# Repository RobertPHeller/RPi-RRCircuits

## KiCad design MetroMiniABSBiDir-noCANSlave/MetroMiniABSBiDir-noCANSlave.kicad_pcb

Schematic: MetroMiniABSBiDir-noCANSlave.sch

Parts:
C1, C2, C3, C4: .1 uf
C5: .1 uf; Mouser Part Number 581-SR295E104MAA
CON1: 7-12 V Power Bus; Mouser Part Number 490-PJ-037A
D1: BRIDGE; Mouser Part Number 750-KBL401-G
D2: DIODESCH; Mouser Part Number SB240-E3/54
IC1: MCT6H; DIP-8__300; Mouser Part Number 782-MCT6H
P1: In Track Out; Mouser Part Number 710-691249510002
P2: +5V EG EY ER WG WY WR GND; Mouser Part Number 651-1725711
P3: Next East
P4, P6: ABS Slave Bus
P5: Next West
R1: 10 Ohms; Mouser Part Number 660-MF1/4LCT52R100J
R2: 10K Ohms; Mouser Part Number 660-MF1/4LCT52R103J
R3, R4, R5, R6, R7, R8: 150 Ohms; Mouser Part Number 660-MF1/4LCT52R151J
SW1: BC CA 0 1 2 3 4 5
T1: - 7-12V +
U1: METROMINI
U2: SN75LBC179; Mouser Part Number 595-SN75LBC179P
U3: TRS202E; Mouser Part Number 595-TRS202ECN

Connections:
+5V: C5.1, P2.1, R2.1, U1.25 (5V), U2.1 (Vcc), U3.16 (Vcc)
/East Green: P2.2, R8.1
/East Red: P2.4, R6.1
/East Yellow: P2.3, R7.1
/West Green: P2.5, R5.1
/West Red: P2.7, R3.1
/West Yellow: P2.6, R4.1
GND: C2.2, C4.2, C5.2, CON1.2, IC1.5, IC1.8, P2.8, P3.1, P3.4, P4.5, P5.1, P5.4, P6.5, SW1.1, SW1.2, SW1.3, SW1.4, SW1.5, SW1.6, SW1.7, SW1.8, T1.2 (PM), U1.23 (GND), U1.24 (GND), U2.4 (GND), U3.15 (GND)
unnamed: P3.2, U3.8 (RIN2)
unnamed: P5.2, U3.14 (DOUT1)
unnamed: P5.3, U3.13 (RIN1)
unnamed: P3.3, U3.7 (DOUT2)
unnamed: U1.13 (#1), U2.3 (D)
unnamed: U1.14 (#0), U2.2 (R)
unnamed: P4.4, P6.4, U2.5 (Y)
unnamed: C1.1, U3.1 (C1+)
unnamed: C3.1, U3.4 (C2+)
unnamed: C3.2, U3.5 (C2-)
unnamed: C1.2, U3.3 (C1-)
unnamed: C4.1, U3.6 (V-)
unnamed: C2.1, U3.2 (V+)
unnamed: U1.10 (#4), U3.12 (ROUT1)
unnamed: U1.7 (#7), U3.9 (ROUT2)
unnamed: SW1.12, U1.18 (A2)
unnamed: SW1.11, U1.17 (A3)
unnamed: SW1.10, U1.16 (A4)
unnamed: SW1.9, U1.15 (A5)
unnamed: SW1.13, U1.19 (A1)
unnamed: SW1.16, U1.2 (#12)
unnamed: SW1.15, U1.12 (#2)
unnamed: SW1.14, U1.20 (A0)
unnamed: CON1.1, D2.1 (A), T1.1
unnamed: P4.2, P6.2, U2.7 (B)
unnamed: P4.3, P6.3, U2.6 (Z)
unnamed: P4.1, P6.1, U2.8 (A)
unnamed: D1.1 (+), D1.4 (-)
unnamed: R8.2, U1.11 (#3)
unnamed: R4.2, U1.4 (#10)
unnamed: R3.2, U1.3 (#11)
unnamed: D2.2 (K), U1.22 (Vin)
unnamed: R7.2, U1.9 (#5)
unnamed: R6.2, U1.8 (#6)
unnamed: R5.2, U1.5 (#9)
unnamed: D1.3, P1.1, R1.1
unnamed: IC1.6, IC1.7, R2.2, U1.6 (#8), U3.10 (DIN2), U3.11 (DIN1)
unnamed: D1.2, IC1.2, IC1.4, P1.2 (PM)
unnamed: IC1.1, IC1.3, R1.2

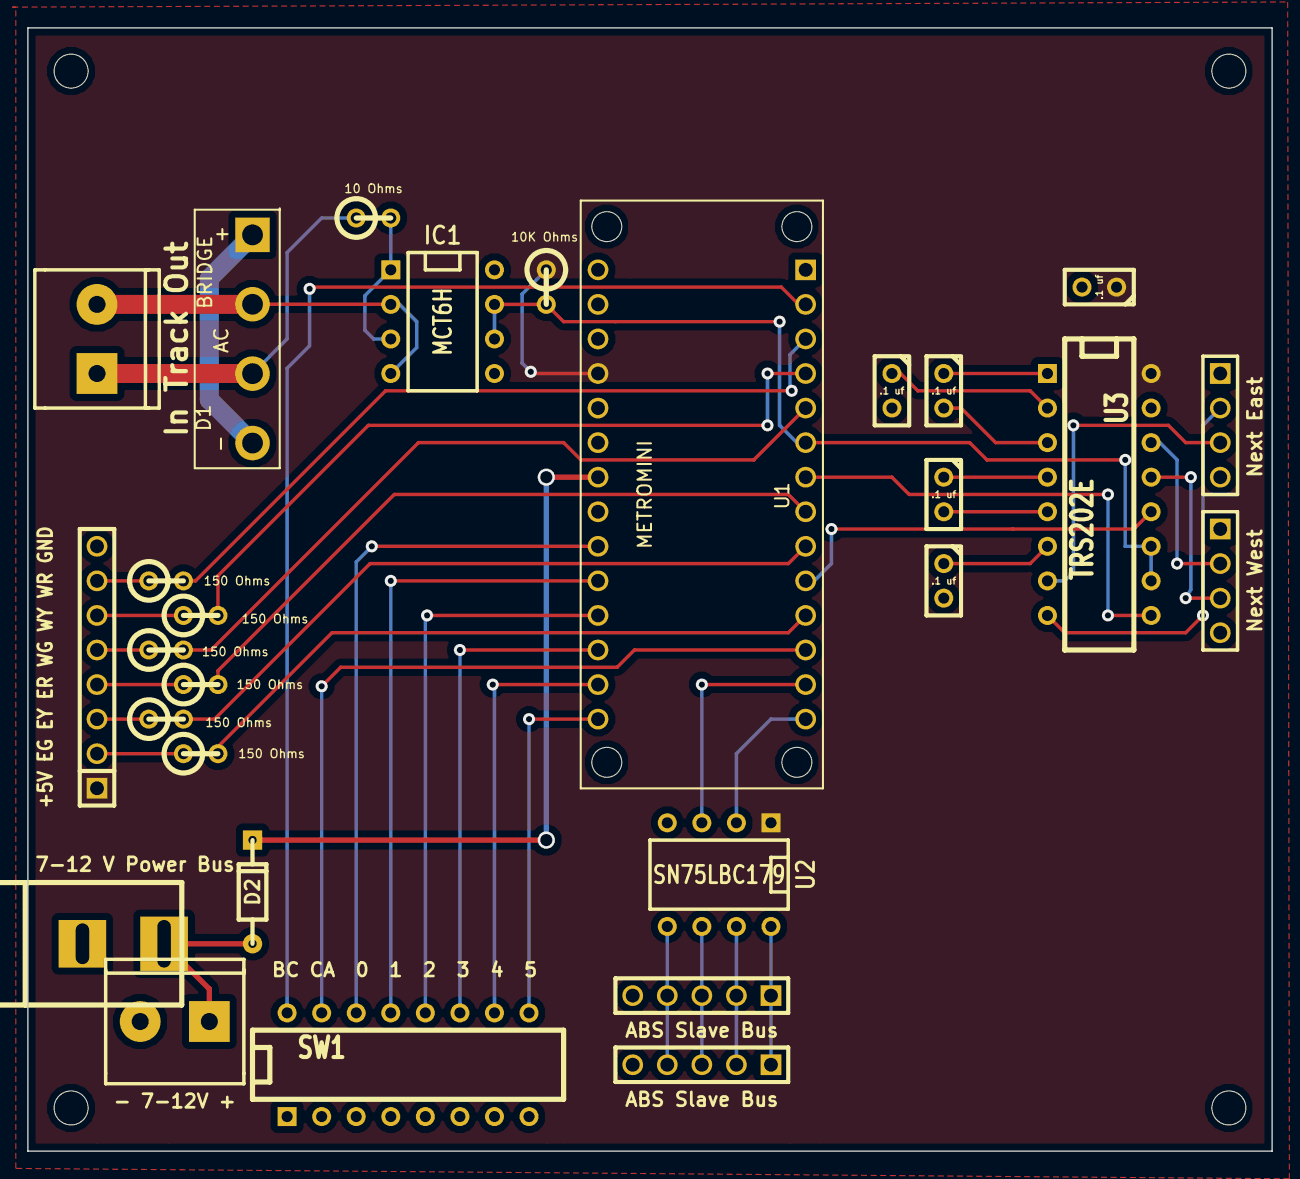
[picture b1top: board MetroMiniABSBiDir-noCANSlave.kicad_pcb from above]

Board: 2 copper layers, 91.4 x 82.5 mm, 32 parts (0 on the bottom side), 47 nets.

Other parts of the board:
MH: MountingHole_2-5mm_RevA_Date21Jun2010
MH#2, MH#3, MH#4: MountingHole_2-5mm_RevA_Date21Jun2010

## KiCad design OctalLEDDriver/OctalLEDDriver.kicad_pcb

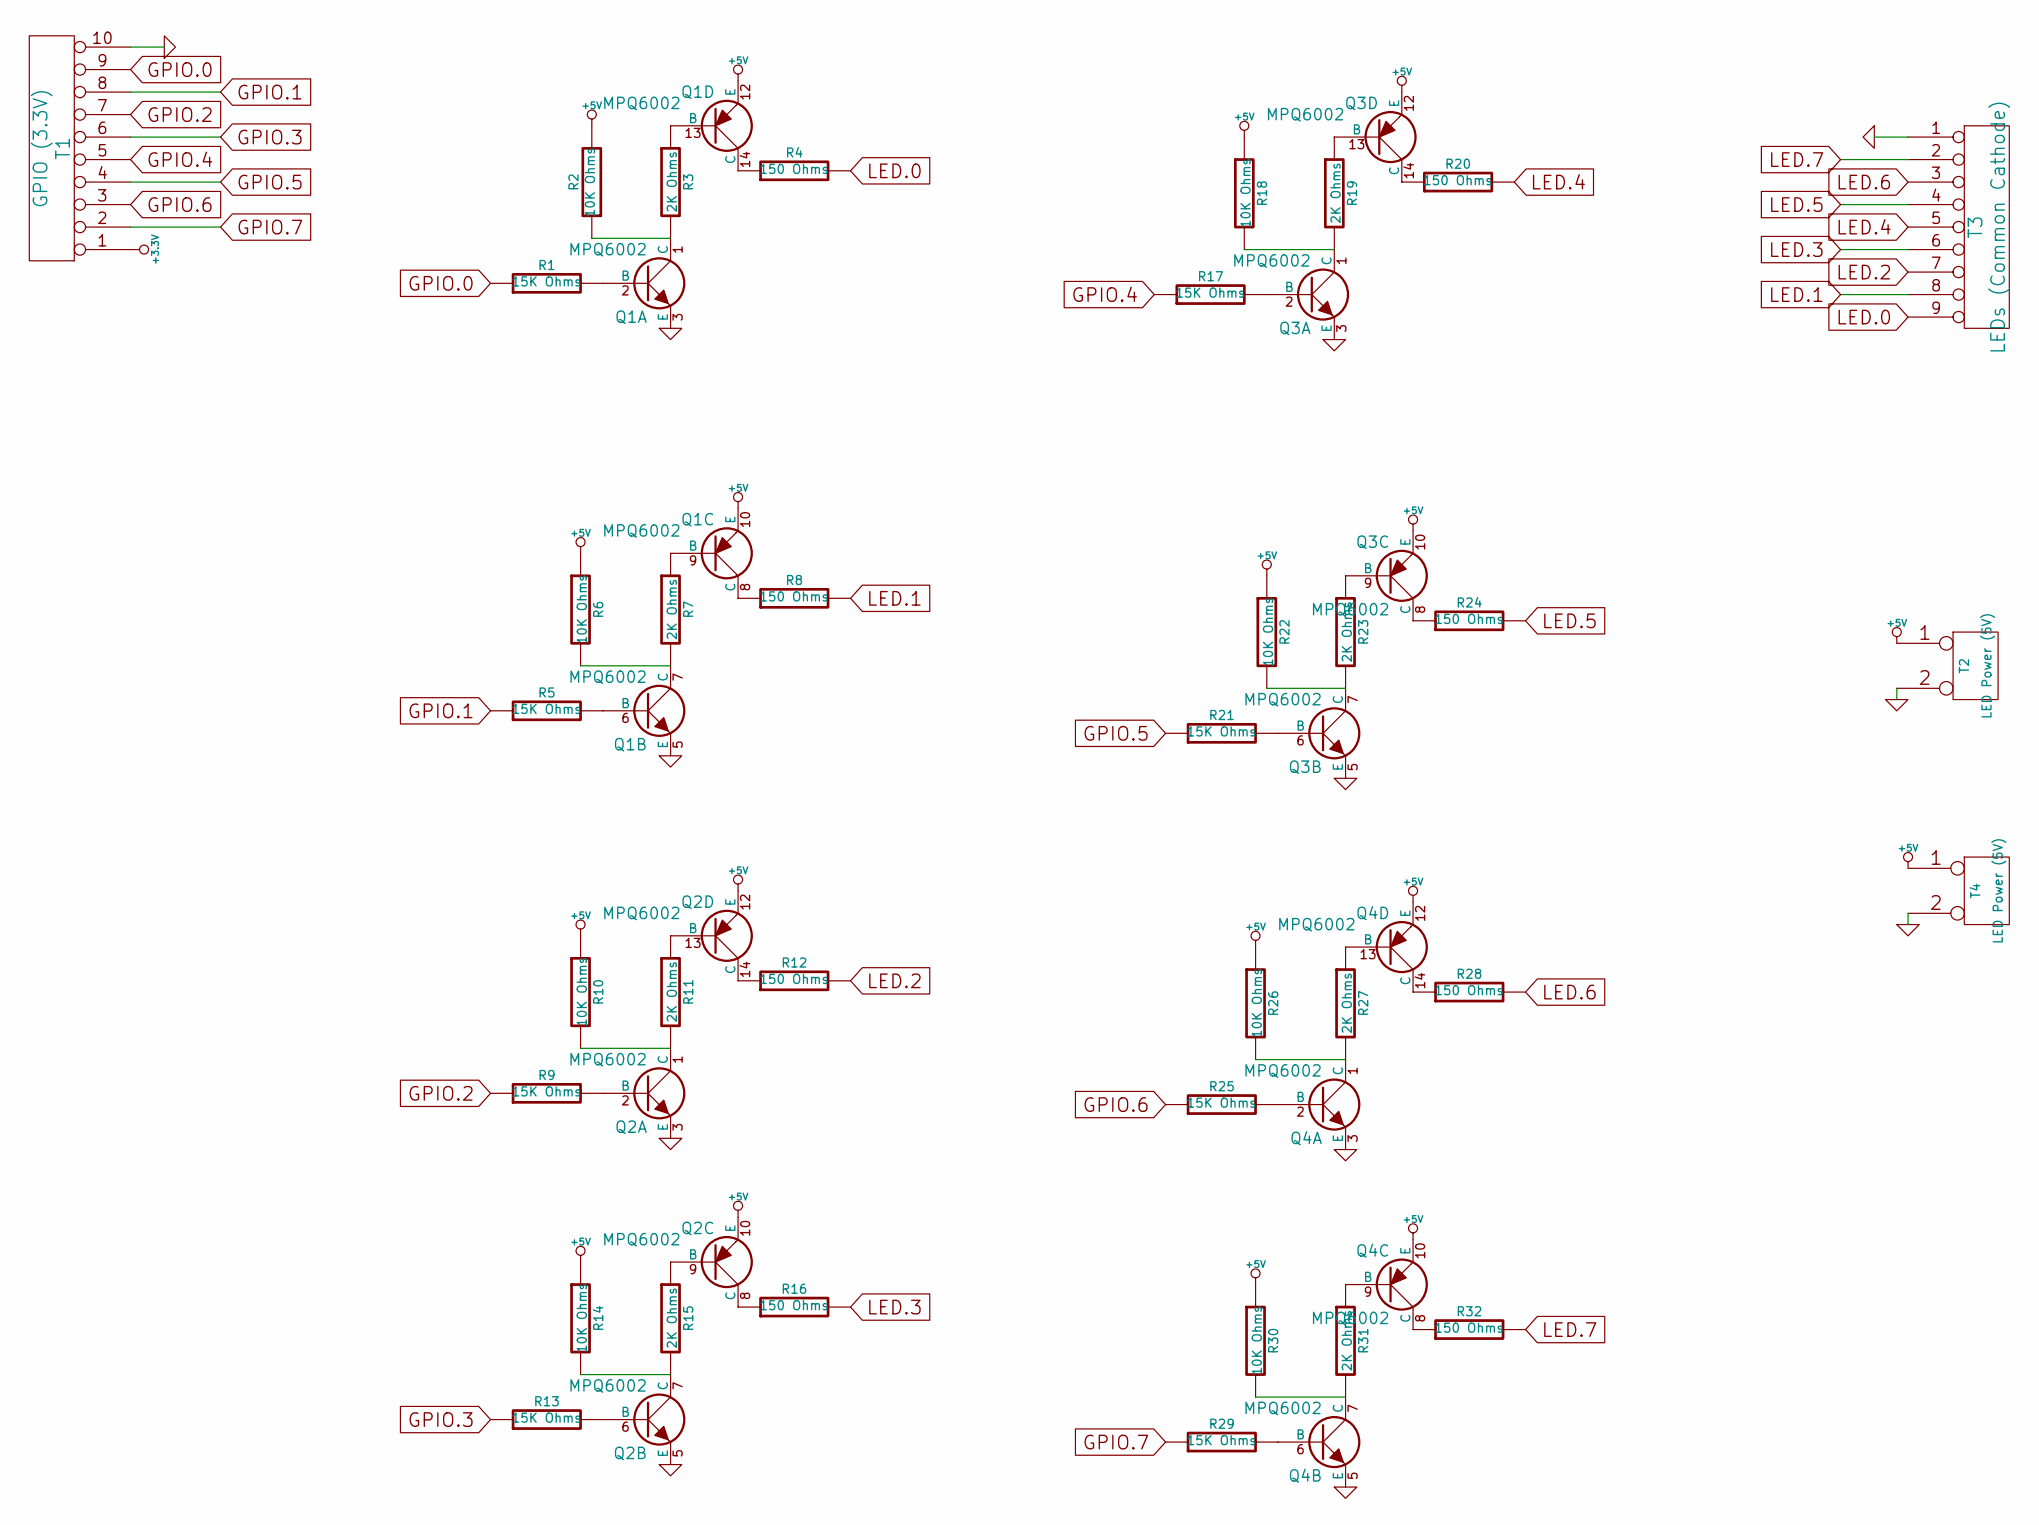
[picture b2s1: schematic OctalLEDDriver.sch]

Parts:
Q1, Q2, Q3, Q4: MPQ6002; Mouser part Number 610-MPQ6002
R1, R5, R9, R13, R17, R21, R25, R29: 15K Ohms; Mouser Part Number 603-CFR-25JR-5215K
R2, R6, R10, R14, R18, R22, R26, R30: 10K Ohms; Mouser Part Number 603-CFR-25JR-5210K
R3, R7, R11, R15, R19, R23, R27, R31: 2K Ohms; Mouser Part Number 603-CFR-25JR-522K
R4, R8, R12, R16, R20, R24, R28, R32: 150 Ohms; Mouser Part Number 588-OK1515E-R52
T1: GPIO (3.3V); Mouser Part Number 651-1725737
T2, T4: LED Power (5V); Mouser part Number 651-1725656
T3: LEDs (Common Cathode); Mouser part Number 651-1725724

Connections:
+5V: Q1.10 (E), Q1.12 (E), Q2.10 (E), Q2.12 (E), Q3.10 (E), Q3.12 (E), Q4.10 (E), Q4.12 (E), R2.2, R6.1, R10.1, R14.1, R18.1, R22.1, R26.1, R30.1, T2.1, T4.1; also elsewhere on the board
GND: Q1.3 (E), Q1.5 (E), Q2.3 (E), Q2.5 (E), Q3.3 (E), Q3.5 (E), Q4.3 (E), Q4.5 (E), T1.10, T2.2 (PM), T3.1, T4.2 (PM); also elsewhere on the board
GPIO.0: R1.1, T1.9
GPIO.1: R5.1, T1.8
GPIO.2: R9.1, T1.7
GPIO.3: R13.1, T1.6
GPIO.4: R17.1, T1.5
GPIO.5: R21.1, T1.4
GPIO.6: R25.1, T1.3
GPIO.7: R29.1, T1.2
LED.0: R4.2, T3.9
LED.1: R8.2, T3.8
LED.2: R12.2, T3.7
LED.3: R16.2, T3.6
LED.4: R20.2, T3.5
LED.5: R24.2, T3.4
LED.6: R28.2, T3.3
LED.7: R32.2, T3.2
unnamed: Q2.7 (C), R14.2, R15.2
unnamed: Q2.8 (C), R16.1
unnamed: Q3.8 (C), R24.1
unnamed: Q3.9 (B), R23.1
unnamed: Q4.8 (C), R32.1
unnamed: Q4.9 (B), R31.1
unnamed: Q3.1 (C), R18.2, R19.2
unnamed: Q3.14 (C), R20.1
unnamed: Q3.7 (C), R22.2, R23.2
unnamed: Q4.1 (C), R26.2, R27.2
unnamed: Q4.14 (C), R28.1
unnamed: Q4.7 (C), R30.2, R31.2
unnamed: Q3.6 (B), R21.2
unnamed: Q4.2 (B), R25.2
unnamed: Q4.13 (B), R27.1
unnamed: Q4.6 (B), R29.2
unnamed: Q1.13 (B), R3.1
unnamed: Q3.13 (B), R19.1
unnamed: Q2.9 (B), R15.1
unnamed: Q2.13 (B), R11.1
unnamed: Q1.9 (B), R7.1
unnamed: Q1.2 (B), R1.2
unnamed: Q1.6 (B), R5.2
unnamed: Q1.14 (C), R4.1
unnamed: Q1.8 (C), R8.1
unnamed: Q2.2 (B), R9.2
unnamed: Q2.14 (C), R12.1
unnamed: Q2.6 (B), R13.2
unnamed: Q3.2 (B), R17.2
unnamed: Q1.7 (C), R6.2, R7.2
unnamed: Q2.1 (C), R10.2, R11.2
unnamed: Q1.1 (C), R2.1, R3.2

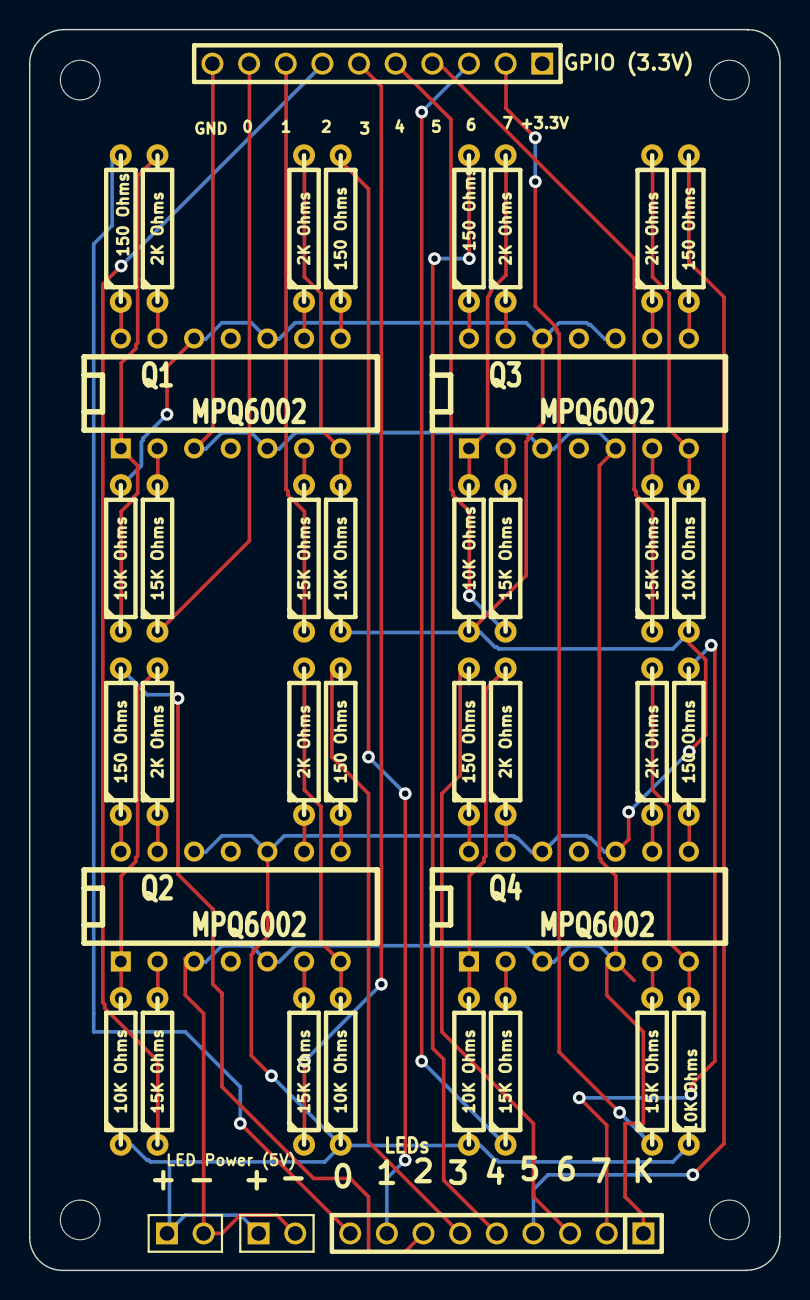
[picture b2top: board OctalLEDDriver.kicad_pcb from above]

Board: 2 copper layers, 52.0 x 86.0 mm, 40 parts (0 on the bottom side), 50 nets.

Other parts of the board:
T2#2: LED Power (5V); ScrewTerm2.54-2

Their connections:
+5V: T2#2.1; also elsewhere on the board
GND: T2#2.2; also elsewhere on the board

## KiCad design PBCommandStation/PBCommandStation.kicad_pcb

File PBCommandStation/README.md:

# PBCommandStation

Original through hole version of the Pocket Beagle LCC/DCC Command Station.
This design is depreciated -- see PocketBeagleCommandStation and 
PocketBeagleCommandStation_SMD for a current design.

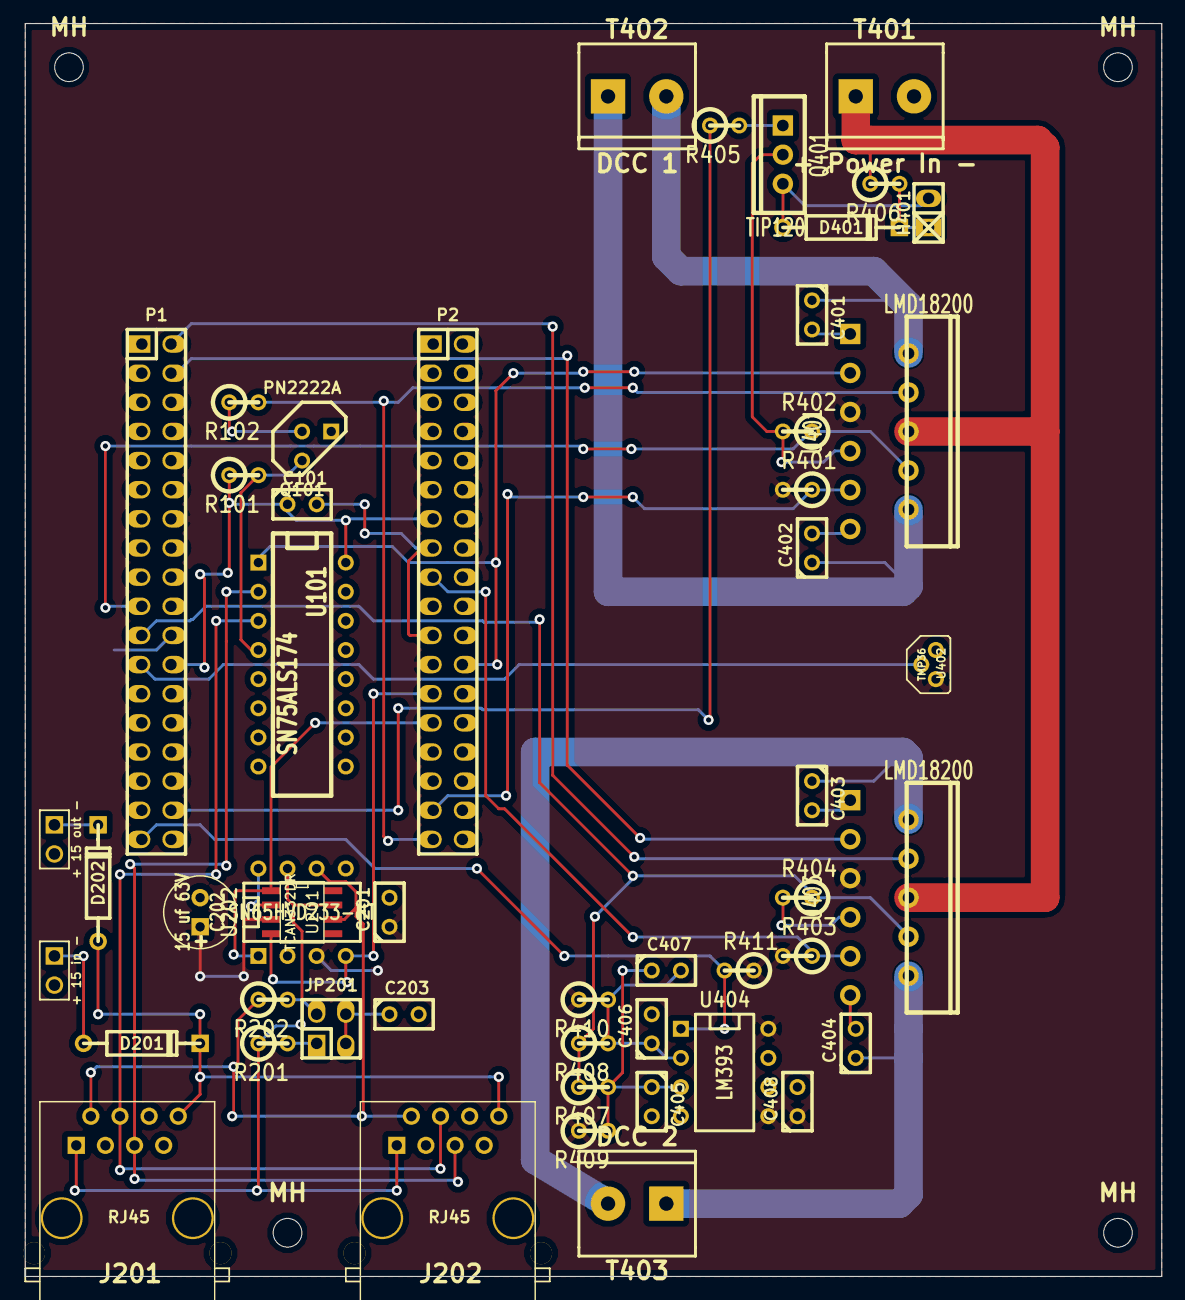
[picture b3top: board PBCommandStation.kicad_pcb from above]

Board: 2 copper layers, 99.1 x 109.2 mm, 54 parts (0 on the bottom side), 42 nets.

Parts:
C101, C201: .1 uf; C1
C202: 15 uf 63V; C1V7
C203: 47 nf; C1
C401, C402, C403, C404: .01 uf; C1
C405, C407: 10 nf; C1
C406: 1 uf; C1
C408: 1000 nf; C1
D201, D202: SB240E; DO-41
D401: 1n5349; DO-41
H401: Fan; pin_strip_2
J201, J202: RJ45; RJ45_8N-S
JP201: Termination; pin_socket_2x2
MH: MountingHole_2-5mm_RevA_Date21Jun2010
MH#2, MH#3, MH#4: MountingHole_2-5mm_RevA_Date21Jun2010
P1: POCKETBEAGLE-P1; pin_socket_18x2
P2: POCKETBEAGLE-P2; pin_socket_18x2
Q101: PN2222A; TO92
Q401: TIP120; TO220_VERT
R101, R102, R405: 1K Ohms; R1
R201, R202: 60 Ohms; R1
R401, R403, R407, R411: 10K Ohms; R1
R402, R404: 1.591K Ohms; R1
R406: 33 Ohms 1W; R1
R408: 13K Ohms; R1
R409, R410: 1M Ohms; R1
T201: + 15 in -; ScrewTerm2.54-2
T202: + 15 out -; ScrewTerm2.54-2
T401: + Power In -; mors_2p
T402: DCC 1; mors_2p
T403: DCC 2; mors_2p
U101: SN75ALS174; DIP-16__300
U201: TCAN332DR; SOIC-8_N
U202: SN65HVD233-HT; DIP-8__300
U401, U403: LMD18200; TO220_11PIN_VERT
U402: TMP36; TO92PN
U404: LM393; DIP-8__300

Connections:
+3.3V: C201.1, C202.1, C408.1, P1.14, P2.23, R401.2, R403.2, R409.1, R410.1, R411.1, U201.3, U202.3, U401.5, U402.1, U403.5, U404.5, U404.8
+5V: C101.1, P1.24, P2.13, R101.1, U101.16
+12V: D201.2, D202.1, J201.8, J202.8
/CAN Transciver/Alt_H: J201.5, J202.5, U101.2
/CAN Transciver/Alt_L: J201.4, J202.4, U101.3
/CAN Transciver/CANH: J201.1, J202.1, R201.1, U201.7, U202.7
/CAN Transciver/CANL: J201.2, J202.2, R202.1, U201.6, U202.6
/CAN Transciver/CAN_RX: P2.25, U201.4, U202.4
/CAN Transciver/CAN_TX: P2.27, U201.1, U202.1
/Dual Booster/Ack Detect: P1.35, R411.2, U404.1
/Dual Booster/Current Sense 1: P1.19, R402.1, U401.8
/Dual Booster/Current Sense 2: P1.21, R404.1, R407.1, R408.1, U403.8
/Dual Booster/DCC Signal 1: P2.24, U101.1, U401.3
/Dual Booster/DCC Signal 2: P1.4, U403.3
/Dual Booster/Enable 1: P2.35, R102.2, U401.4
/Dual Booster/Enable 2: P1.2, U403.4
/Dual Booster/Fan Control: P1.34, R405.1
/Dual Booster/Temp Sense: P1.23, U402.2
/Dual Booster/Thermal Flag 1: P2.33, R401.1, U401.9
/Dual Booster/Thermal Flag 2: P2.17, R403.1, U403.9
GND: C101.2, C201.2, C202.2, C203.2, C405.2, C406.2, C408.2, J201.3, J201.6, J201.7, J202.3, J202.6, J202.7, P1.15, P1.16, P1.22, P2.15, P2.21, Q401.3, R402.2, R404.2, T201.2, T202.2, T401.2, U101.8, U201.2, U202.2, U202.5, U202.8, U401.7, U402.3, U403.7, U404.4, U404.6
unnamed: Q101.2, R102.1
unnamed: Q101.3, R101.2, U101.4
unnamed: D201.1, T201.1
unnamed: D202.2, T202.1
unnamed: JP201.1, R201.2
unnamed: JP201.2, R202.2
unnamed: C203.1, JP201.3, JP201.4
unnamed: C405.1, C407.1, R407.2, R409.2, U404.3
unnamed: D401.1, H401.2, Q401.2
unnamed: D401.2, H401.1, R406.2
unnamed: Q401.1, R405.2
unnamed: C406.1, C407.2, R408.2, R410.2, U404.2
unnamed: C401.2, U401.1
unnamed: C402.2, U401.11
unnamed: C401.1, T402.2, U401.2
unnamed: C402.1, T402.1, U401.10
unnamed: C403.1, T403.2, U403.2
unnamed: C403.2, U403.1
unnamed: C404.1, T403.1, U403.10
unnamed: C404.2, U403.11
VCOM: R406.1, T401.1, U401.6, U403.6

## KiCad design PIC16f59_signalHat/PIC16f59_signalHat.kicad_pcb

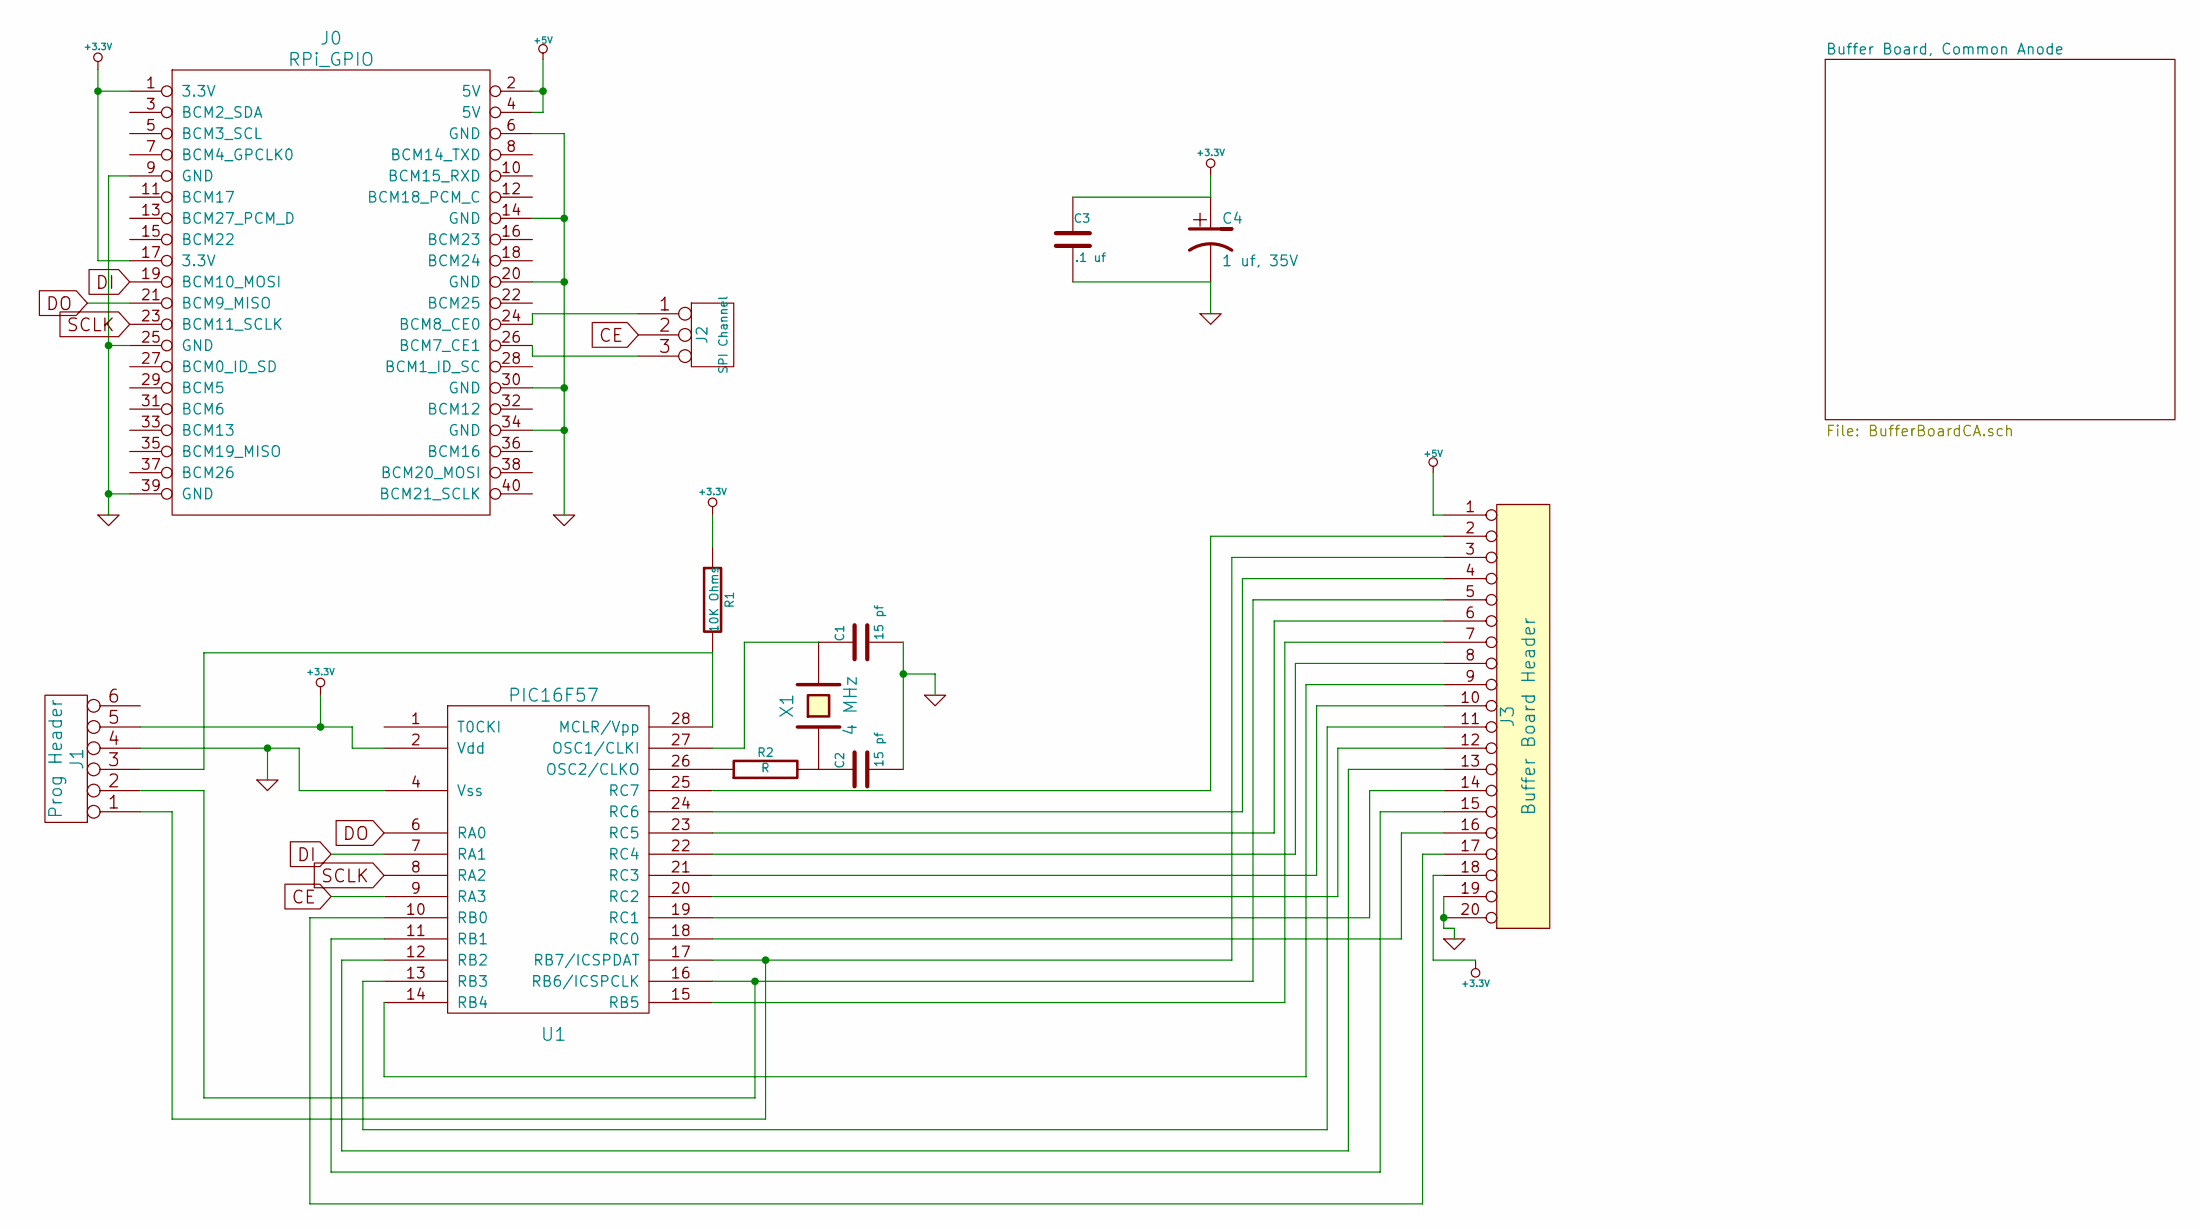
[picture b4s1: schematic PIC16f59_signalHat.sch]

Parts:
C1, C2: 15 pf
C3: .1 uf
C4: 1 uf, 35V
J0: RPi_GPIO; Pin_Header_Straight_2x20
J1: Prog Header; PIN_ARRAY_3x2
J2: SPI Channel; PIN_ARRAY_3x1
J3: Buffer Board Header; PIN_ARRAY_10x2
R1: 10K Ohms
R2: R
U1: PIC16F57
X1: 4 MHz; HC-49V; Mouser Part Number 449-LFXTAL033206BULK

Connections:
+3.3V: C3.1, C4.1, J0.1 (3.3V), J0.17 (3.3V), J1.5, J3.18, R1.1, U1.2 (Vdd)
+5V: J0.2 (5V), J0.4 (5V), J3.1
CE: J2.2 (PM), U1.9 (RA3)
DI: J0.19 (BCM10_MOSI), U1.7 (RA1)
DO: J0.21 (BCM9_MISO), U1.6 (RA0)
GND: C1.2, C2.2, C3.2, C4.2, J0.6 (GND), J0.9 (GND), J0.14 (GND), J0.20 (GND), J0.25 (GND), J0.30 (GND), J0.34 (GND), J0.39 (GND), J1.4, J3.19, J3.20, U1.4 (Vss)
unnamed: J3.10, U1.21 (RC3)
unnamed: J3.8, U1.22 (RC4)
unnamed: J3.6, U1.23 (RC5)
unnamed: J3.4, U1.24 (RC6)
unnamed: J3.2, U1.25 (RC7)
unnamed: J3.11, U1.13 (RB3)
unnamed: J3.9, U1.14 (RB4)
unnamed: J3.7, U1.15 (RB5)
unnamed: J0.26 (BCM7_CE1), J2.3
unnamed: J0.24 (BCM8_CE0), J2.1
unnamed: J1.1, J3.3, U1.17 (RB7/ICSPDAT)
unnamed: J1.2, J3.5, U1.16 (RB6/ICSPCLK)
unnamed: J1.3, R1.2, U1.28 (MCLR/Vpp)
unnamed: C2.1, R2.2, X1.1
unnamed: C1.1, U1.27 (OSC1/CLKI), X1.2
unnamed: R2.1, U1.26 (OSC2/CLKO)
unnamed: J3.16, U1.18 (RC0)
unnamed: J3.14, U1.19 (RC1)
unnamed: J3.12, U1.20 (RC2)
unnamed: J3.13, U1.12 (RB2)
unnamed: J3.17, U1.10 (RB0)
unnamed: J3.15, U1.11 (RB1)
SCLK: J0.23 (BCM11_SCLK), U1.8 (RA2)

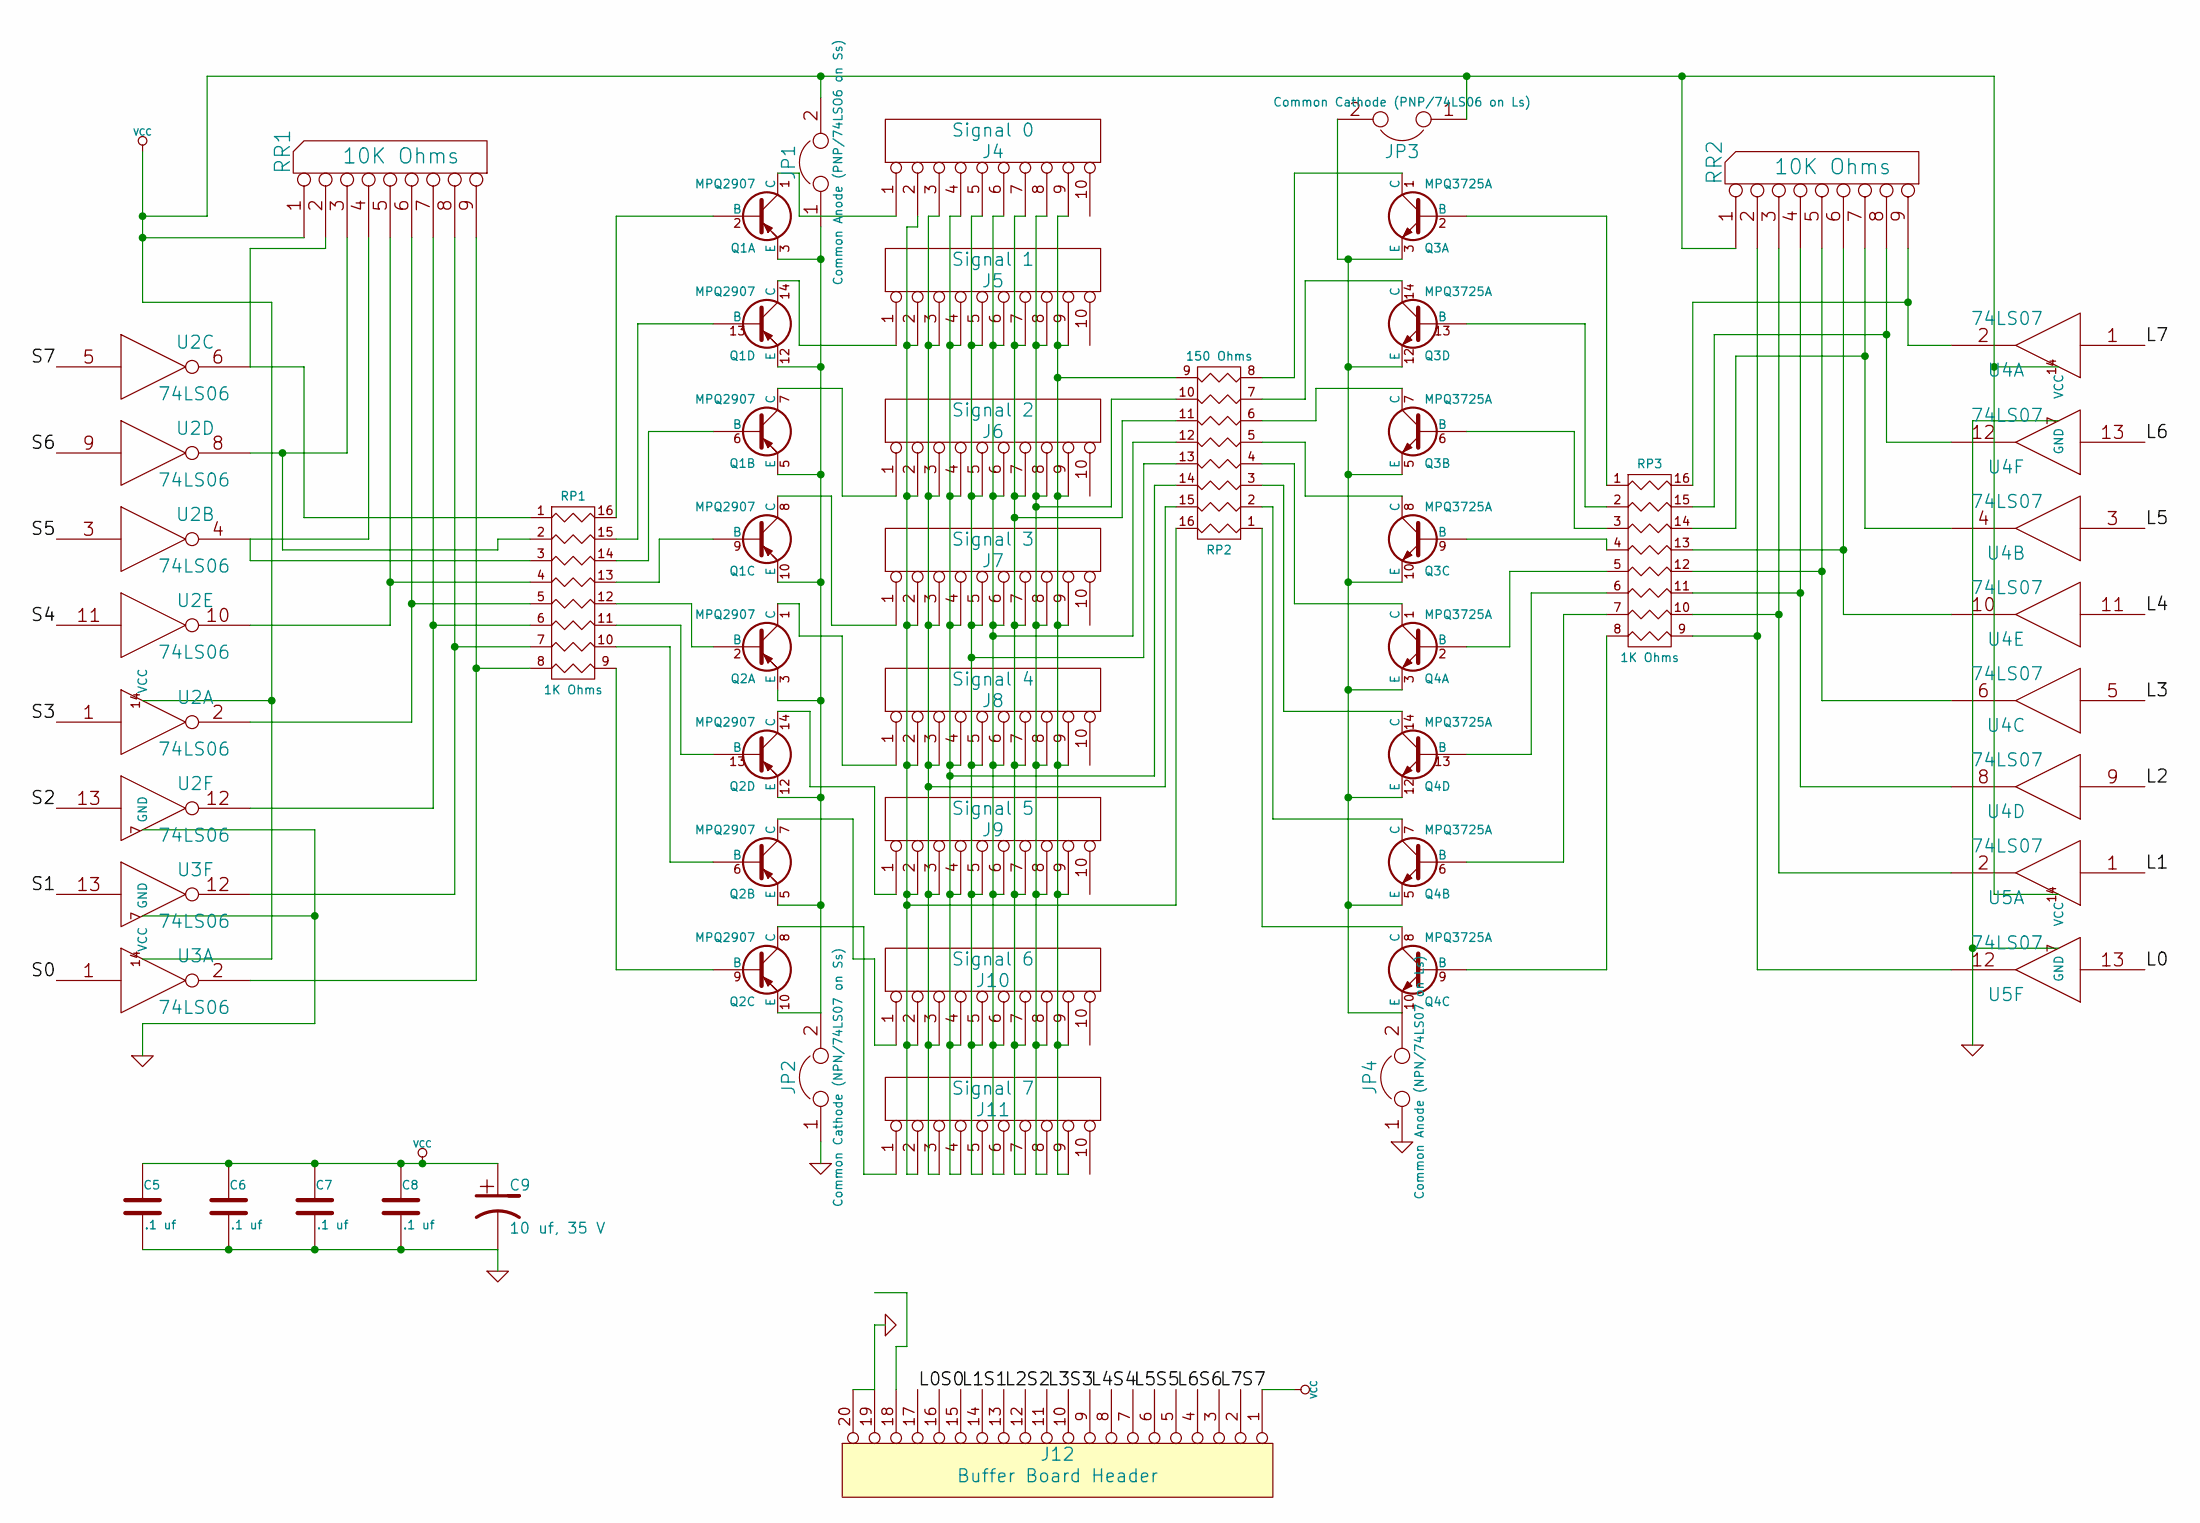
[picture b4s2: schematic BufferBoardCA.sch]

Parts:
C5, C6, C7, C8: .1 uf
C9: 10 uf, 35 V
J4: Signal 0; PIN_ARRAY_5X2
J5: Signal 1; PIN_ARRAY_5X2
J6: Signal 2; PIN_ARRAY_5X2
J7: Signal 3; PIN_ARRAY_5X2
J8: Signal 4; PIN_ARRAY_5X2
J9: Signal 5; PIN_ARRAY_5X2
J10: Signal 6; PIN_ARRAY_5X2
J11: Signal 7; PIN_ARRAY_5X2
J12: Buffer Board Header; PIN_ARRAY_10x2
JP1: Common Anode (PNP/74LSO6 on Ss)
JP2: Common Cathode (NPN/74LS07 on Ss)
JP3: Common Cathode (PNP/74LS06 on Ls)
JP4: Common Anode (NPN/74LS07 on Ls)
Q1, Q2: MPQ2907; DIP-14__300
Q3, Q4: MPQ3725A; DIP-14__300
RP1, RP3: 1K Ohms; DIP-16__300; Mouser Part Number 652-4116R-1LF-1K
RP2: 150 Ohms; DIP-16__300; Mouser Part Number 652-4116R-1LF-150
RR1, RR2: 10K Ohms; SIL-9
U2: 74LS06; DIP-14__300
U3: 74LS06; DIP-14_300
U4, U5: 74LS07; DIP-14_300

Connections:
/Buffer Board, Common Anode/L0: J12.17, U5.13
/Buffer Board, Common Anode/L1: J12.15, U5.1
/Buffer Board, Common Anode/L2: J12.13, U4.9
/Buffer Board, Common Anode/L3: J12.11, U4.5
/Buffer Board, Common Anode/L4: J12.9, U4.11
/Buffer Board, Common Anode/L5: J12.7, U4.3
/Buffer Board, Common Anode/L6: J12.5, U4.13
/Buffer Board, Common Anode/L7: J12.3, U4.1
/Buffer Board, Common Anode/S0: J12.16, U3.1
/Buffer Board, Common Anode/S1: J12.14, U3.13
/Buffer Board, Common Anode/S2: J12.12, U2.13
/Buffer Board, Common Anode/S3: J12.10, U2.1
/Buffer Board, Common Anode/S4: J12.8, U2.11
/Buffer Board, Common Anode/S5: J12.6, U2.3
/Buffer Board, Common Anode/S6: J12.4, U2.9
/Buffer Board, Common Anode/S7: J12.2, U2.5
GNDA: C5.2, C6.2, C7.2, C8.2, C9.2, J12.19, J12.20, JP2.1, JP4.1, U2.7 (GND), U3.7 (GND), U4.7 (GND), U5.7 (GND)
unnamed: J4.1, Q1.1 (C)
unnamed: J5.1, Q1.14 (C)
unnamed: J6.1, Q1.7 (C)
unnamed: J7.1, Q1.8 (C)
unnamed: JP3.2, JP4.2, Q3.3 (E), Q3.5 (E), Q3.10 (E), Q3.12 (E), Q4.3 (E), Q4.5 (E), Q4.10 (E), Q4.12 (E)
unnamed: J8.1, Q2.1 (C)
unnamed: J9.1, Q2.14 (C)
unnamed: J10.1, Q2.7 (C)
unnamed: J11.1, Q2.8 (C)
unnamed: Q2.6 (B), RP1.10 (R7)
unnamed: Q2.9 (B), RP1.9 (R8)
unnamed: Q1.2 (B), RP1.16 (R1)
unnamed: Q1.13 (B), RP1.15 (R2)
unnamed: Q1.6 (B), RP1.14 (R3)
unnamed: Q1.9 (B), RP1.13 (R4)
unnamed: Q2.2 (B), RP1.12 (R5)
unnamed: Q2.13 (B), RP1.11 (R6)
unnamed: Q3.9 (B), RP3.4
unnamed: Q4.2 (B), RP3.5
unnamed: Q4.13 (B), RP3.6
unnamed: Q4.6 (B), RP3.7
unnamed: Q4.9 (B), RP3.8
unnamed: JP1.1, JP2.2, Q1.3 (E), Q1.5 (E), Q1.10 (E), Q1.12 (E), Q2.3 (E), Q2.5 (E), Q2.10 (E), Q2.12 (E)
unnamed: Q3.2 (B), RP3.1
unnamed: Q3.13 (B), RP3.2
unnamed: Q3.6 (B), RP3.3
unnamed: J4.2, J5.2, J6.2, J7.2, J8.2, J9.2, J10.2, J11.2, RP2.16 (R1)
unnamed: Q3.7 (C), RP2.6
unnamed: Q3.14 (C), RP2.7
unnamed: Q3.1 (C), RP2.8
unnamed: Q4.8 (C), RP2.1
unnamed: Q4.7 (C), RP2.2
unnamed: Q4.14 (C), RP2.3
unnamed: Q4.1 (C), RP2.4
unnamed: Q3.8 (C), RP2.5
unnamed: J4.3, J5.3, J6.3, J7.3, J8.3, J9.3, J10.3, J11.3, RP2.15 (R2)
unnamed: J4.4, J5.4, J6.4, J7.4, J8.4, J9.4, J10.4, J11.4, RP2.14 (R3)
unnamed: J4.7, J5.7, J6.7, J7.7, J8.7, J9.7, J10.7, J11.7, RP2.11 (R6)
unnamed: J4.6, J5.6, J6.6, J7.6, J8.6, J9.6, J10.6, J11.6, RP2.12 (R5)
unnamed: J4.5, J5.5, J6.5, J7.5, J8.5, J9.5, J10.5, J11.5, RP2.13 (R4)
unnamed: J4.9, J5.9, J6.9, J7.9, J8.9, J9.9, J10.9, J11.9, RP2.9 (R8)
unnamed: J4.8, J5.8, J6.8, J7.8, J8.8, J9.8, J10.8, J11.8, RP2.10 (R7)
unnamed: RP3.13 (R4), RR2.6, U4.10
unnamed: RP3.14 (R3), RR2.7, U4.4
unnamed: RP3.15 (R2), RR2.8, U4.12
unnamed: RP3.16 (R1), RR2.9, U4.2
unnamed: RP1.1, RR1.2, U2.6
unnamed: RP1.2, RR1.3, U2.8
unnamed: RP1.3, RR1.4, U2.4
unnamed: RP1.4, RR1.5, U2.10
unnamed: RP1.5, RR1.6, U2.2
unnamed: RP1.6, RR1.7, U2.12
unnamed: RP1.7, RR1.8, U3.12
unnamed: RP1.8, RR1.9, U3.2
unnamed: RP3.9 (R8), RR2.2, U5.12
unnamed: RP3.10 (R7), RR2.3, U5.2
unnamed: RP3.11 (R6), RR2.4, U4.8
unnamed: RP3.12 (R5), RR2.5, U4.6
VCC: C5.1, C6.1, C7.1, C8.1, C9.1, J12.1, JP1.2, JP3.1, RR1.1 (COM), RR2.1 (COM), U2.14 (VCC), U3.14 (VCC), U4.14 (VCC), U5.14 (VCC)

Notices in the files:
PocketBeagleMultifuntion/PocketBeagleMultifuntion.kicad_pcb:
(C) 2021 Deepwoods Software
